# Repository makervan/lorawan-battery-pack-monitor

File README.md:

# LoRaWAN Battery Pack Monitor
The LoRaWAN Battery Pack Monitor is a LoRaWAN connected device based on the ATMega328 LoRaWAN Node to automatically measure the individual cell voltages of a Lithium Ion battery pack (up to 7S).

Find more details in the [MakerVan Labs Wiki](https://wiki.makervan.de/wiki/LoRaWAN_Battery_Monitor)

## License
* Licensed under Creative Commons Attribution-ShareAlike 4.0 Unported License (CC BY-SA 4.0)
* [Severin Schols](https://github.com/tiefpunkt)

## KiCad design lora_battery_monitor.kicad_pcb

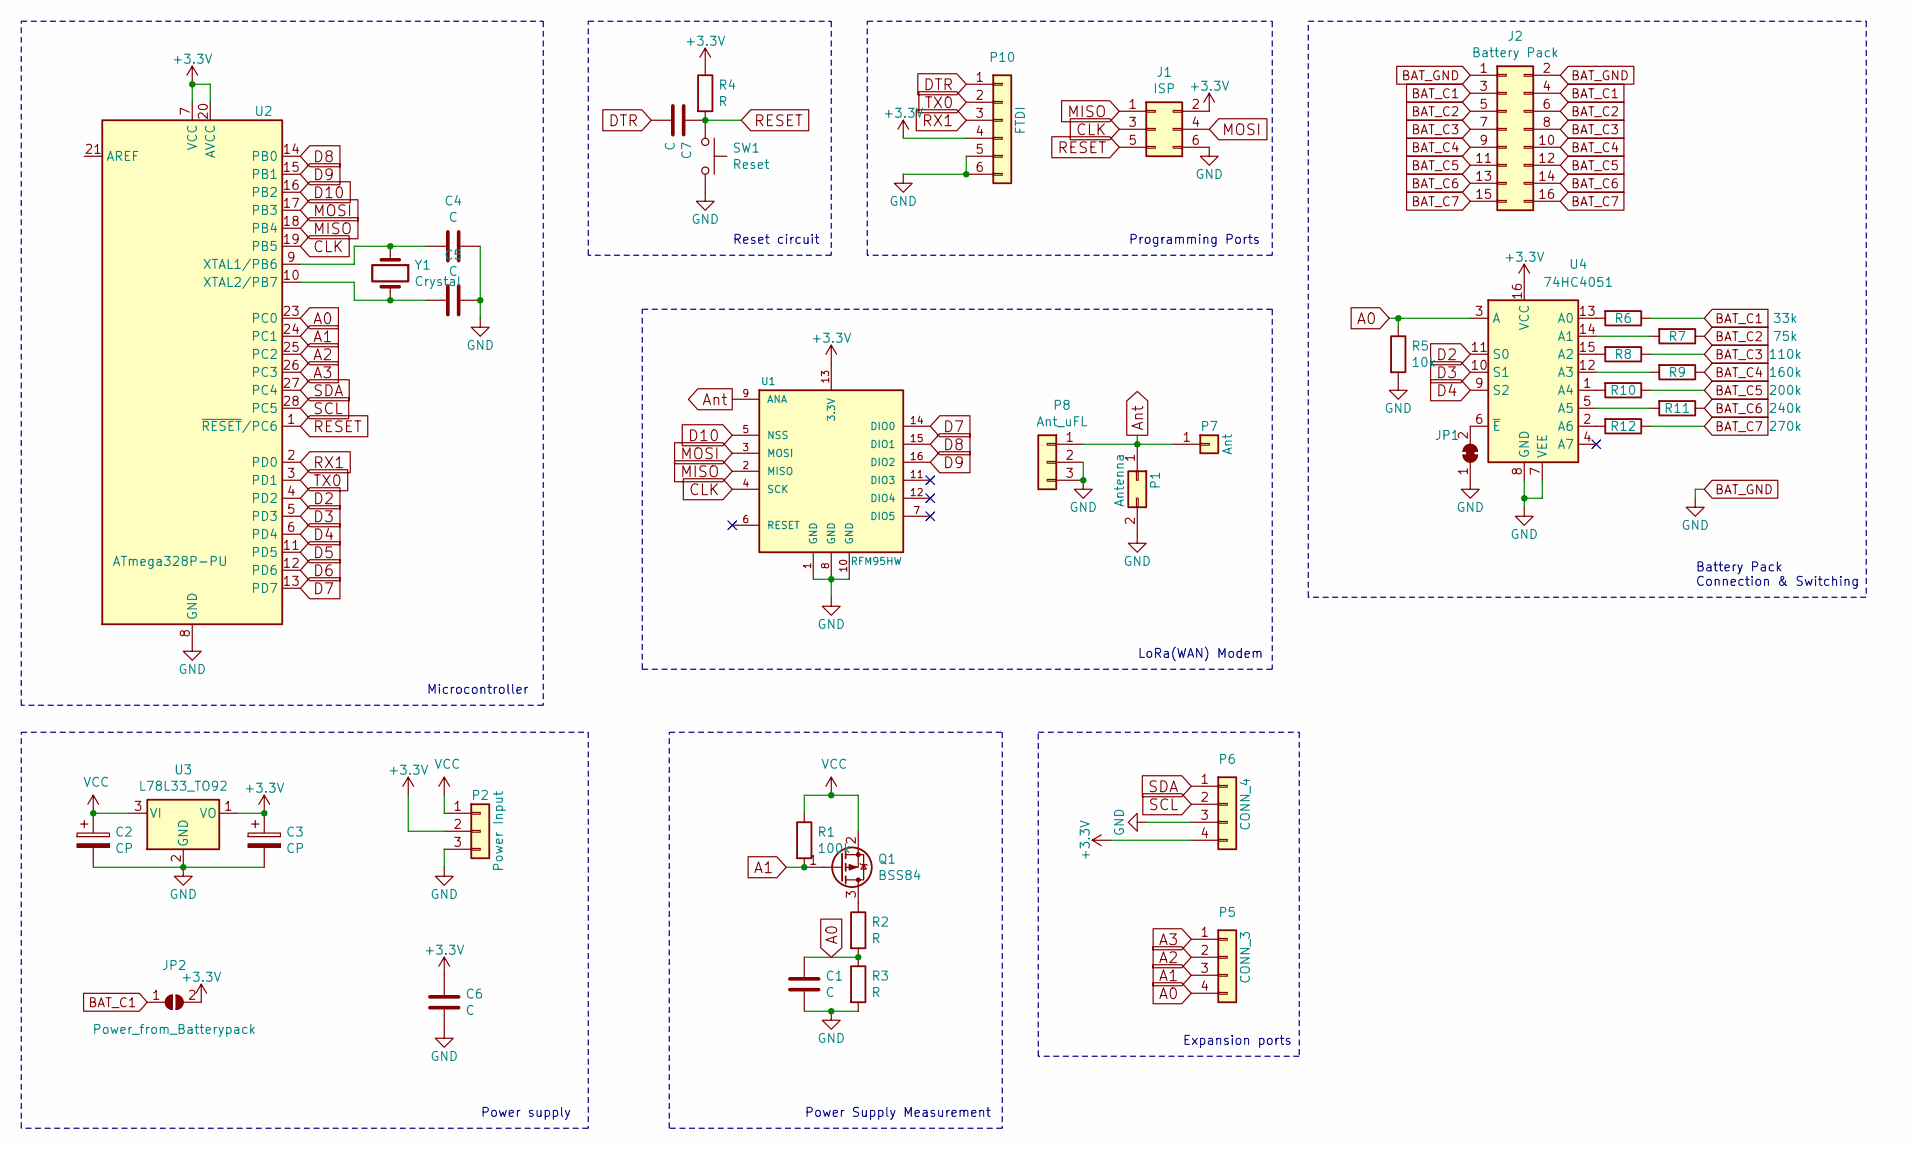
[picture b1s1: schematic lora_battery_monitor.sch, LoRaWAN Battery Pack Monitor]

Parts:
C1, C4, C5, C6, C7: C; C_0805_2012Metric_Pad1.15x1.40mm_HandSolder
C2, C3: CP; CP_Radial_D5.0mm_P2.50mm
J1: ISP; PinHeader_2x03_P2.54mm_Vertical
J2: Battery Pack; IDC-Header_2x08_P2.54mm_Vertical
JP1: Enable_jumper; SolderJumper-2_P1.3mm_Bridged_RoundedPad1.0x1.5mm
JP2: Power_from_Batterypack; SolderJumper-2_P1.3mm_Open_RoundedPad1.0x1.5mm
P1: Antenna; SMA_EDGE
P2: Power Input; PINHEAD1-3
P5: CONN_3; Pin_Header_Straight_1x04
P6: CONN_4; Pin_Header_Straight_1x04
P7: Ant; PINTST
P8: Ant_uFL; U.FL-COAX
P10: FTDI; PinHeader_1x06_P2.54mm_Vertical
Q1: BSS84; SOT-23
R1: 100k; R_0805_2012Metric_Pad1.15x1.40mm_HandSolder
R2, R3, R4: R; R_0805_2012Metric_Pad1.15x1.40mm_HandSolder
R5: 10k; R_0805_2012Metric_Pad1.20x1.40mm_HandSolder
R6: 33k; R_0805_2012Metric_Pad1.20x1.40mm_HandSolder
R7: 75k; R_0805_2012Metric_Pad1.20x1.40mm_HandSolder
R8: 110k; R_0805_2012Metric_Pad1.20x1.40mm_HandSolder
R9: 160k; R_0805_2012Metric_Pad1.20x1.40mm_HandSolder
R10: 200k; R_0805_2012Metric_Pad1.20x1.40mm_HandSolder
R11: 240k; R_0805_2012Metric_Pad1.20x1.40mm_HandSolder
R12: 270k; R_0805_2012Metric_Pad1.20x1.40mm_HandSolder
SW1: Reset; SW_PUSH_6mm
U1: RFM95HW; RFM69HW_SMD_Handsoldering-Narrow
U2: ATmega328P-PU; DIP-28_W7.62mm
U3: L78L33_TO92; TO-92_Inline
U4: 74HC4051; SO-16_3.9x9.9mm_P1.27mm
Y1: Crystal; Crystal_HC49-U_Vertical

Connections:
+3V3: C3.1, C6.2, J1.2, JP2.2 (B), P2.2, P6.4, P10.4, R4.1, U1.13 (3.3V), U2.7 (VCC), U2.20 (AVCC), U3.1 (VO), U4.16 (VCC)
A0: C1.1, P5.4, R2.2, R3.1, R5.1, U2.23 (PC0), U4.3 (A)
A1: P5.3, Q1.1 (G), R1.2, U2.24 (PC1)
A2: P5.2, U2.25 (PC2)
A3: P5.1, U2.26 (PC3)
Ant: P1.1, P7.1, P8.1, U1.9 (ANA)
BAT_C1: J2.3, J2.4, JP2.1 (A), R6.1
BAT_C2: J2.5, J2.6, R7.1
BAT_C3: J2.7, J2.8, R8.1
BAT_C4: J2.9, J2.10, R9.1
BAT_C5: J2.11, J2.12, R10.1
BAT_C6: J2.13, J2.14, R11.1
BAT_C7: J2.15, J2.16, R12.1
BAT_GND: C1.2, C2.2, C3.2, C4.1, C5.1, C6.1, J1.6, J2.1, J2.2, JP1.1 (A), P1.2, P2.3, P6.3, P8.2, P8.3, P10.5, P10.6, R3.2, R5.2, SW1.2, U1.1 (GND), U1.8 (GND), U1.10 (GND), U2.8 (GND), U2.22 (GND), U3.2 (GND), U4.7 (VEE), U4.8 (GND)
CLK: J1.3, U1.4 (SCK), U2.19 (PB5)
D2: U2.4 (PD2), U4.11 (S0)
D3: U2.5 (PD3), U4.10 (S1)
D4: U2.6 (PD4), U4.9 (S2)
D5: U2.11 (PD5)
D6: U2.12 (PD6)
D7: U1.14 (DIO0), U2.13 (PD7)
D8: U1.15 (DIO1), U2.14 (PB0)
D9: U1.16 (DIO2), U2.15 (PB1)
D10: U1.5 (NSS), U2.16 (PB2)
DTR: C7.1, P10.1
MISO: J1.1, U1.2 (MISO), U2.18 (PB4)
MOSI: J1.4, U1.3 (MOSI), U2.17 (PB3)
unnamed: C4.2, U2.9 (XTAL1/PB6), Y1.1
unnamed: C5.2, U2.10 (XTAL2/PB7), Y1.2
unnamed: JP1.2 (B), U4.6 (~E)
unnamed: Q1.3 (D), R2.1
unnamed: R6.2, U4.13 (A0)
unnamed: R7.2, U4.14 (A1)
unnamed: R8.2, U4.15 (A2)
unnamed: R9.2, U4.12 (A3)
unnamed: R10.2, U4.1 (A4)
unnamed: R11.2, U4.5 (A5)
unnamed: R12.2, U4.2 (A6)
RESET: C7.2, J1.5, R4.2, SW1.1, U2.1 (~RESET~/PC6)
RX1: P10.3, U2.2 (PD0)
SCL: P6.2, U2.28 (PC5)
SDA: P6.1, U2.27 (PC4)
TX0: P10.2, U2.3 (PD1)
VCC: C2.1, P2.1, Q1.2 (S), R1.1, U3.3 (VI)

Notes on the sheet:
Microcontroller
Reset circuit
Programming Ports
LoRa(WAN) Modem
Power supply
Power Supply Measurement
Battery Pack Connection & Switching
Expansion ports

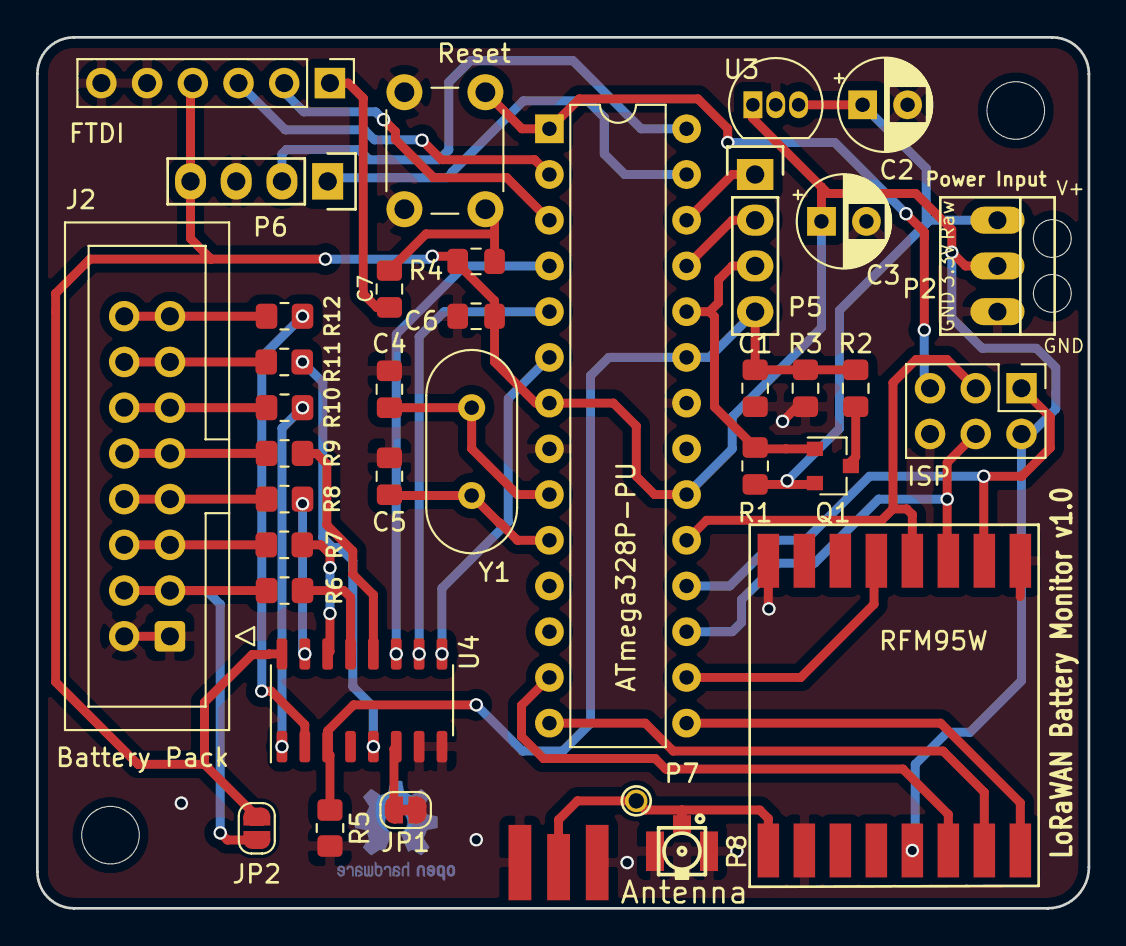
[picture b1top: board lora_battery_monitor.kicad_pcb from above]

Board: 2 copper layers, 58.4 x 48.4 mm, 37 parts (0 on the bottom side), 42 nets.
